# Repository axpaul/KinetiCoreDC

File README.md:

# KinetiCoreDC

🌐 **Langue / Language :** [🇫🇷 Français](README.md) | [🇬🇧 English](README.en.md)

---

**KinetiCoreDC** est un contrôleur de moteur DC durci en boucle fermée permettant de transformer tout moteur à balais en un **servomoteur intelligent** (asservissement en position, vitesse et couple). Développé par **Paul Miailhe** pour **Berry Rocket**.

© 2025/2026 - **Paul Miailhe** (*Berry Rocket*).  
This material is licensed under the **CERN Open Hardware Licence Version 2 - Strongly Reciprocal (CERN-OHL-S)**. $\rightarrow$ [LICENSE](LICENSE)

---

## 1. Vue d'ensemble & Applications

Articulée autour d'un microcontrôleur **STM32G070CBT6** (ARM Cortex-M0+ @ $64\text{ MHz}$, horloge interne HSI) et d'un pont en H intégré **DRV8874PWPR**, la carte intègre l'ensemble de l'électronique de puissance, de protection et de conditionnement nécessaire au pilotage précis d'un actionneur DC en environnement embarqué :

- **Servomoteur numérique multi-axes :** Asservissement PID (position / vitesse / couple) piloté et supervisé sur bus différentiel RS-485 (`THVD1400D`, jusqu'à $500\text{ kbps}$).
- **Actionnement sécurisé ou redondant :** Pilotage par consigne PWM ou impulsion RC ($1\text{–}2\text{ ms}$) via deux entrées opto-isolées (`TLP2310`) autorisant une voie de commande secondaire de secours.
- **Mécatronique & Robotique mobile :** Contrôle de moteurs DC avec retour d'encodeur absolu (`AS5047P`, `AS5600`) ou incrémental Hall, prise d'origine (*homing*) sur butées mécaniques et limitation d'effort par mesure de courant (`IPROPI`).

---

## 2. Caractéristiques électriques

L'étage d'entrée est dimensionné pour une alimentation sur batterie **LiPo 2S ou 3S** (ou source DC régulée). Un contrôleur **LTC4365TS8** associé à deux MOSFETs N-Channel tête-bêche (**SiS412DN**) assure la coupure matérielle en cas de sous-tension, surtension ou inversion de polarité, tandis qu'une diode TVS **SMBJ15CA** protège le régulateur $+3{,}3\text{ V}$ contre les transitoires.

| Paramètre | Symbole | Min | Typ | Max | Unité | Conditions / Notes |
| :--- | :--- | :---: | :---: | :---: | :---: | :--- |
| **Tension d'entrée** | $V_{\text{IN}}$ | $5{,}90$ | $7{,}4\text{–}11{,}1$ | **$14{,}75$** | $\text{V}$ | Compatible LiPo 2S ($8{,}4\text{ V}$) et 3S ($12{,}6\text{ V}$) |
| **Tenue inversion polarité** | $V_{\text{REV}}$ | **$-40$** | — | — | $\text{V}$ | Blocage par N-MOSFETs tête-bêche |
| **Seuil sous-tension (coupure)** | $V_{\text{UVLO}}$ | — | $5{,}90$ | — | $\text{V}$ | Enclenchement à $6{,}20\text{ V}$ (config. défaut) |
| **Seuil surtension (coupure)** | $V_{\text{OVLO}}$ | — | **$14{,}75$** | — | $\text{V}$ | Réarmement à $14{,}01\text{ V}$ (TVS `SMBJ15CA`) |
| **Courant moteur régulé** | $I_{\text{TRIP}}$ | — | **$2{,}6$** | **$2{,}6$** | $\text{A}$ | $V_{\text{REF}} = 2{,}50\text{ V}$, $R_{\text{IPROPI}} = 2{,}49\text{ k}\Omega$ |
| **Courant moteur crête** | $I_{\text{PEAK}}$ | — | — | **$6{,}0$** | $\text{A}$ | Limite silicium `DRV8874` (`XT30` : $15\text{ A}$ cont.) |
| **Puissance d'entrée** | $P_{\text{IN}}$ | — | $32{,}8$ | $38{,}4$ | $\text{W}$ | À $I_{\text{TRIP}} = 2{,}6\text{ A}$ (jusqu'à $88{,}5\text{ W}$ crête à $6\text{ A}$) |
| **Rail logique** | $V_{\text{3V3}}$ | $3{,}28$ | $3{,}30$ | $3{,}32$ | $\text{V}$ | Précision $\pm 0{,}4\text{ \%}$ (`MCP1703A`, boîtier SOT-223) |
| **Courant disponible $+3{,}3\text{ V}$** | $I_{\text{OUT(3V3)}}$ | — | — | **$250$** | $\text{mA}$ | Total carte ($\approx 50\text{ mA}$) + capteurs externes |
| **Courant de veille** | $I_{\text{SHDN}}$ | — | — | **$< 10$** | $\mu\text{A}$ | Broche `SHDN_EXT` tirée à `GND` |

> **Ajustement des seuils :** La fenêtre de protection UVLO/OVLO peut être adaptée à un profil batterie spécifique (LiPo 2S dédié $6{,}45\text{–}10{,}84\text{ V}$, LiPo 3S dédié $9{,}15\text{–}14{,}28\text{ V}$ ou pile 9V) via le pont diviseur du `LTC4365` sur la feuille `Power.kicad_sch`. Le seuil de courant $I_{\text{TRIP}}$ est également ajustable jusqu'à $6\text{ A}$ via `R_IPROPI`.

---

## 3. Interfaces & Capteurs supportés

Toutes les entrées/sorties externes sont équipées de protections contre les décharges électrostatiques (ESD), les inversions de câblage et le bruit de découpage moteur ($32\text{ kHz}$). Les départs d'alimentation $+3{,}3\text{ V}$ vers les capteurs externes (`J10` et `J12`) sont protégés par des résistances série de $22\ \Omega$, tandis que les signaux mécaniques sont filtrés matériellement puis remis en forme par des triggers de Schmitt (**SN74LVC2G14DBV**).

| Connecteur | Interface | Signal / Protocole | Conditionnement & Protection | Compatibilité |
| :--- | :--- | :--- | :--- | :--- |
| **`J2` / `J3`** | `XT30PW-M` (2 pts) | Puissance $V_{\text{IN}}$ / Moteur | TVS `SMBJ15CA`, N-MOSFETs, LEDs sens/PWM | LiPo 2S–3S, moteur DC à balais |
| **`J11`** | `JST-GH` (3 pts) | RS-485 Half-Duplex ($\le 500\text{ kbps}$) | `THVD1400D`, terminaison $120\ \Omega$, TVS `SM712` | Bus multi-axes, télémétrie |
| **`J7` / `J8`** | `JST-GH` (2 pts) | $2\times$ PWM / GPIO isolés ($3{,}3\text{–}5\text{ V}$) | Optocoupleurs `TLP2310`, clamp inverse `SMF6.0A` | Consigne PWM/RC, voie redondante |
| **`J12`** | `JST-GH` (6 pts) | Bus hybride `SPI2` ou `I2C1` | TVS `ESD224DQA` ($0{,}5\text{ pF}$), $+3{,}3\text{ V}$ ($22\ \Omega$), pull-ups `DNP` | **AS5047P**, **AS5048A**, **MA730**, **AS5600** |
| **`J10`** | `JST-GH` (4 pts) | Encodeur quadrature A/B ($3{,}3\text{–}5\text{ V}$) | `USBLC6-2SC6`, $+3{,}3\text{ V}$ ($22\ \Omega$), RC ($160\text{ kHz}$) + Schmitt | Encodeurs incrémentaux à effet Hall |
| **`J4` / `J5`** | `JST-GH` (2 pts) | $2\times$ Fins de course (contact sec) | Pull-up $2{,}2\text{ k}\Omega$, RC ($160\text{ Hz}$) + Schmitt | Butées mécaniques Min / Max |
| **`J9`** | `JST-GH` (3 pts) | Activation carte (`SHDN_EXT`) | Commande directe broche `SHDN` du `LTC4365` | Interrupteur marche / veille |
| **`J6`** | `JST-GH` (2 pts) | Sortie défaut alim (`NFAULT_EXT`) | Drain ouvert actif bas (`LTC4365`) | Supervision système hôte |
| **`J1`** | `TC2070-NL` (14 pts) | SWD + NRST + UART VCP (`USART3`) | Empreinte sans composants (STDC14) | ST-LINK/V3 (flash & debug) |

Pour les capteurs de position absolue sur **`J12`**, le bus fonctionne par défaut en **SPI haute vitesse** (recommandé en environnement bruité pour les **AS5047P** / **MA730**). Il peut être basculé en **I²C** pour un **AS5600** en soudant les deux résistances de pull-up de $4{,}7\text{ k}\Omega$ prévues sur la feuille `Connector.kicad_sch`.

---

## 4. Brochage MCU (`STM32G070CBT6` — LQFP48)

L'affectation des broches du microcontrôleur a été optimisée pour aligner les signaux du pont en H sur le flanc droit du boîtier LQFP48, isoler les canaux analogiques (`ADC_VM` et `IPROPI`) et supprimer tout croisement de pistes vers les connecteurs périphériques.

| Bloc fonctionnel | Signal | Broche | Périphérique | Fonction |
| :--- | :--- | :---: | :--- | :--- |
| **Driver Moteur** | `PH/IN2_MCU` | `PA8` (28) | `TIM1_CH1` | Direction (`PH`) ou PWM secondaire |
| | `EN/IN1_MCU` | `PA9` (29) | `TIM1_CH2` | PWM principale moteur ($32\text{ kHz}$) |
| | `NSLEEP_MCU` | `PC6` (30) | `GPIO_Output` | Activation / Veille du pont en H |
| | `PMODE_MCU` | `PC7` (31) | `GPIO_Output` | Mode `PH/EN` (`0`) ou `PWM` (`1`) |
| | `NFAULT_MCU` | `PA10` (32) | `GPIO_EXTI10` | Interruption défaut driver (front descendant) |
| | `IPROPI_MCU` | `PB10` (22) | `ADC1_IN11` | Lecture courant moteur ($1{,}13\text{ V/A}$, filtre RC) |
| **Supervision** | `ADC_VM` | `PB2` (21) | `ADC1_IN10` | Mesure tension d'entrée $V_M$ |
| **RS-485** | `RS485_DE` / `TX` / `RX` | `PA1`, `PA2`, `PA3` | `USART2` (+ DMA) | Bus différentiel avec contrôle DE matériel |
| **Encodeur** | `TIM_ENC_A` / `B` | `PA6` (17), `PA7` (18) | `TIM3_CH1/CH2` | Décodage quadrature matériel X4 |
| **Optocoupleurs** | `OPTO1_MCU` / `OPTO2_MCU` | `PB14` (26), `PB15` (27) | `TIM15_CH1/CH2` | Input Capture PWM / Consigne redondante |
| **Fins de course** | `TRIG1_MCU` / `TRIG2_MCU` | `PD2` (40), `PD3` (41) | `GPIO_EXTI2/EXTI3` | Interruptions butées (front montant) |
| **Bus Capteur** | `MISO`/`MOSI`/`SCK`/`NSS` | `PB6`..`PB9` (45–48) | `SPI2` (ou `I2C1`) | Encodeur magnétique absolu |
| **IHM** | `BLUE` / `RED` / `GREEN` | `PC13`, `PC14`, `PC15` | `GPIO_Output` | LED RGB 8 couleurs (anode commune, actif bas) |
| | `BUZZER_MCU` | `PA4` (15) | `TIM14_CH1` | Signal piézo PWM $4\text{ kHz}$ |
| **Debug** | `SWDIO` / `SWCLK` | `PA13` (35), `PA14` (36) | `SYS_SWD` | Programmation et débogage |
| | `VPC_TX` / `VPC_RX` | `PA5` (16), `PB0` (19) | `USART3_TX/RX` | Console série virtuelle de diagnostic |

---

## 5. Architecture KiCad & Structure du dépôt

Le projet est conçu sous **KiCad 10.0** autour d'une feuille racine et de trois sous-feuilles hiérarchiques, accompagnées du fichier de configuration **STM32CubeMX** (`KinetiCoreDC.ioc`) :

```text
KinetiCoreDC/
├── KinetiCoreDC.kicad_pro       # Projet KiCad 10.0
├── KinetiCoreDC.kicad_sch       # Feuille 1/4 : MCU STM32G070CBT6 & hiérarchie
├── Interface.kicad_sch          # Feuille 2/4 : RS-485, optocoupleurs, encodeur, butées
├── Power.kicad_sch              # Feuille 3/4 : LTC4365, LDO 3.3V, DRV8874, RGB, buzzer
├── Connector.kicad_sch          # Feuille 4/4 : XT30, JST-GH, Tag-Connect, ESD224DQA
├── KinetiCoreDC.kicad_pcb       # Routage PCB
├── KinetiCoreDC.ioc             # Configuration matérielle STM32CubeMX
├── Datasheet/                   # Fiches techniques des composants
├── lib/                         # Symboles, empreintes et modèles 3D locaux
├── README.md                    # Documentation française
├── README.en.md                 # Documentation anglaise
└── LICENSE                      # Licence CERN-OHL-S-2.0

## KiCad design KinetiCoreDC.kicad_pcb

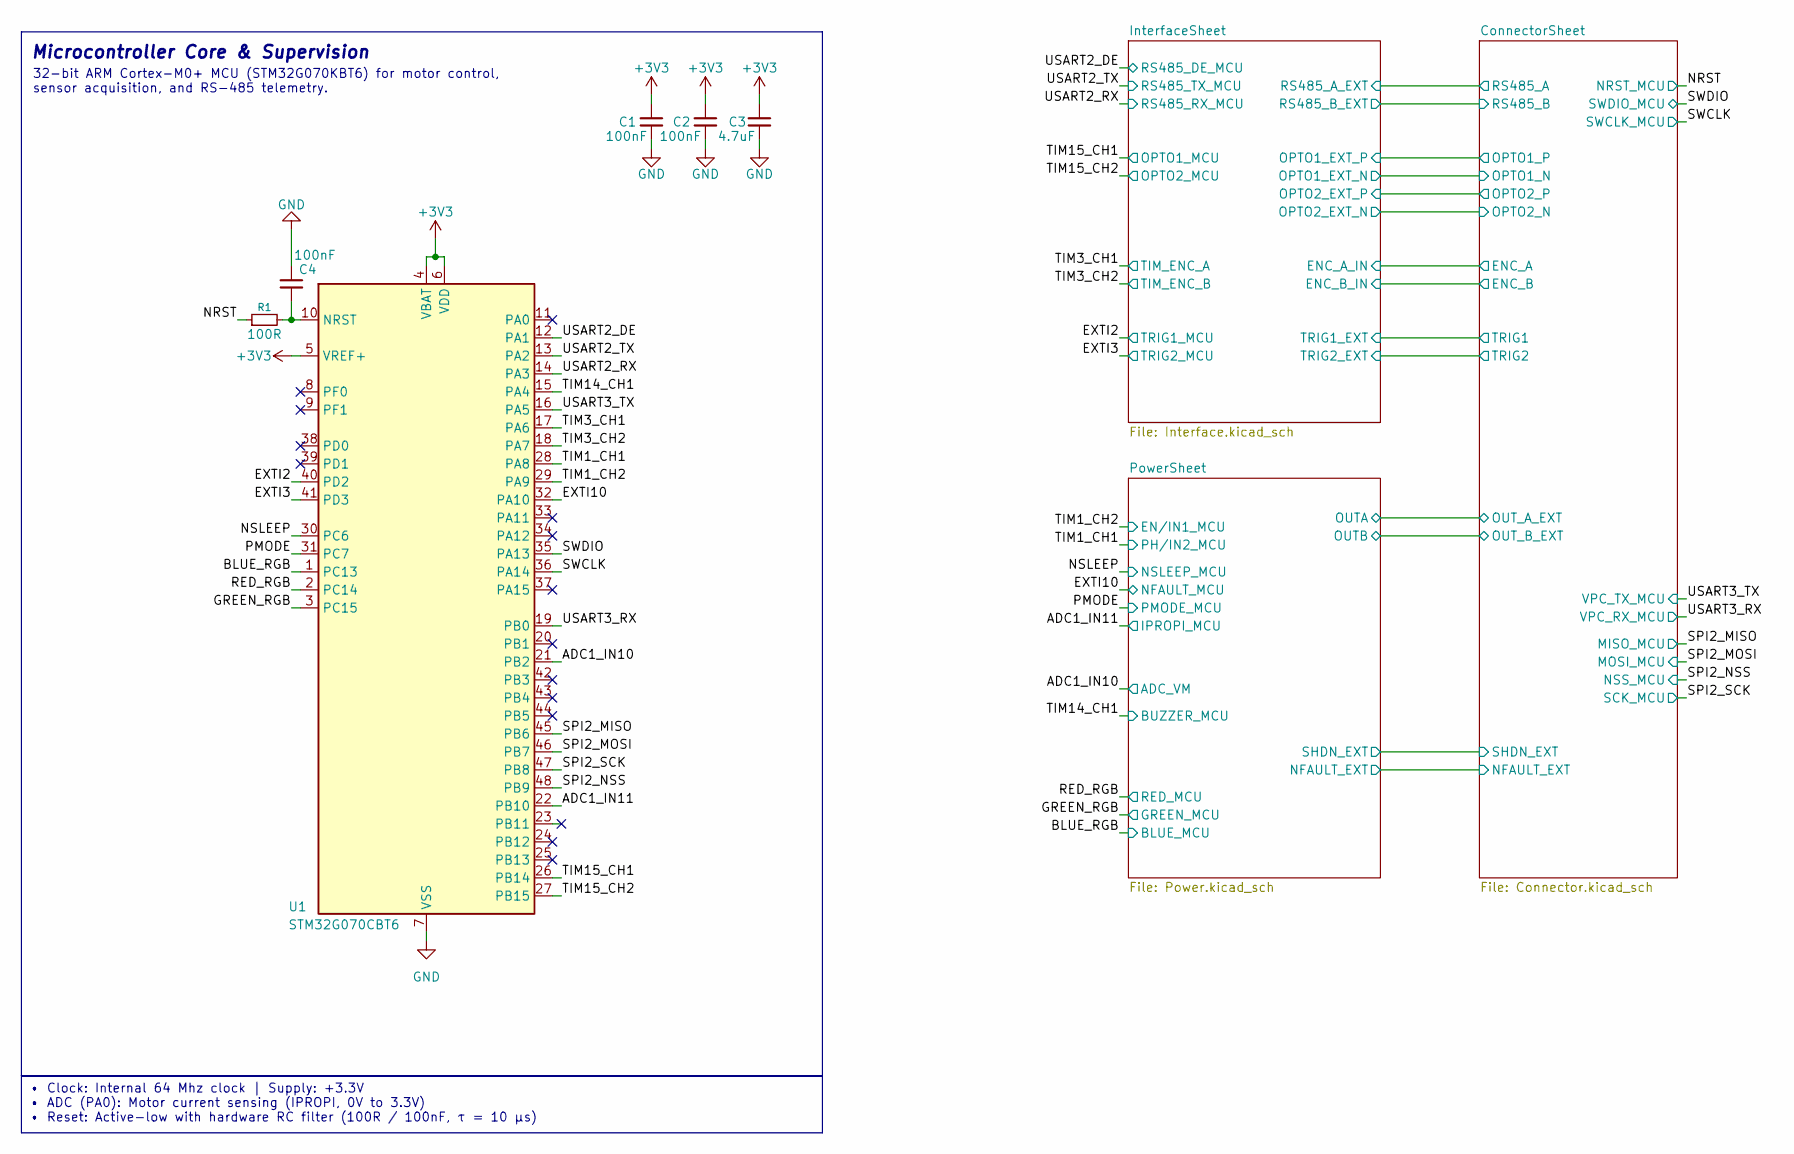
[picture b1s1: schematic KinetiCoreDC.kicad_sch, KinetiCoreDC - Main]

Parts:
C1, C2, C4: 100nF; C_0603_1608Metric
C3: 4.7uF; C_0603_1608Metric
R1: 100R; R_0603_1608Metric
U1: STM32G070CBT6; LQFP-48_7x7mm_P0.5mm

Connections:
+3V3: C1.1, C2.1, C3.1, U1.4 (VBAT), U1.5 (VREF+), U1.6 (VDD); also elsewhere on the board
/ADC1_IN10: U1.21 (PB2); also elsewhere on the board
/ADC1_IN11: U1.22 (PB10); also elsewhere on the board
/BLUE_RGB: U1.1 (PC13); also elsewhere on the board
/EXTI2: U1.40 (PD2); also elsewhere on the board
/EXTI3: U1.41 (PD3); also elsewhere on the board
/EXTI10: U1.32 (PA10); also elsewhere on the board
/GREEN_RGB: U1.3 (PC15); also elsewhere on the board
/NRST: R1.1; also elsewhere on the board
/NSLEEP: U1.30 (PC6); also elsewhere on the board
/PMODE: U1.31 (PC7); also elsewhere on the board
/RED_RGB: U1.2 (PC14); also elsewhere on the board
/SPI2_MISO: U1.45 (PB6); also elsewhere on the board
/SPI2_MOSI: U1.46 (PB7); also elsewhere on the board
/SPI2_NSS: U1.48 (PB9); also elsewhere on the board
/SPI2_SCK: U1.47 (PB8); also elsewhere on the board
/SWCLK: U1.36 (PA14); also elsewhere on the board
/SWDIO: U1.35 (PA13); also elsewhere on the board
/TIM1_CH1: U1.28 (PA8); also elsewhere on the board
/TIM1_CH2: U1.29 (PA9); also elsewhere on the board
/TIM3_CH1: U1.17 (PA6); also elsewhere on the board
/TIM3_CH2: U1.18 (PA7); also elsewhere on the board
/TIM14_CH1: U1.15 (PA4); also elsewhere on the board
/TIM15_CH1: U1.26 (PB14); also elsewhere on the board
/TIM15_CH2: U1.27 (PB15); also elsewhere on the board
/USART2_DE: U1.12 (PA1); also elsewhere on the board
/USART2_RX: U1.14 (PA3); also elsewhere on the board
/USART2_TX: U1.13 (PA2); also elsewhere on the board
/USART3_RX: U1.19 (PB0); also elsewhere on the board
/USART3_TX: U1.16 (PA5); also elsewhere on the board
GND: C1.2, C2.2, C3.2, C4.2, U1.7 (VSS); also elsewhere on the board
unnamed: C4.1, R1.2, U1.10 (NRST)

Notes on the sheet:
Microcontroller Core & Supervision
32-bit ARM Cortex-M0+ MCU (STM32G070KBT6) for motor control, sensor acquisition, and RS-485 telemetry.
• Clock: Internal 64 Mhz clock | Supply: +3.3V • ADC (PA0): Motor current sensing (IPROPI, 0V to 3.3V) • Reset: Active-low with hardware RC filter (100R / 100nF, τ = 10 µs)

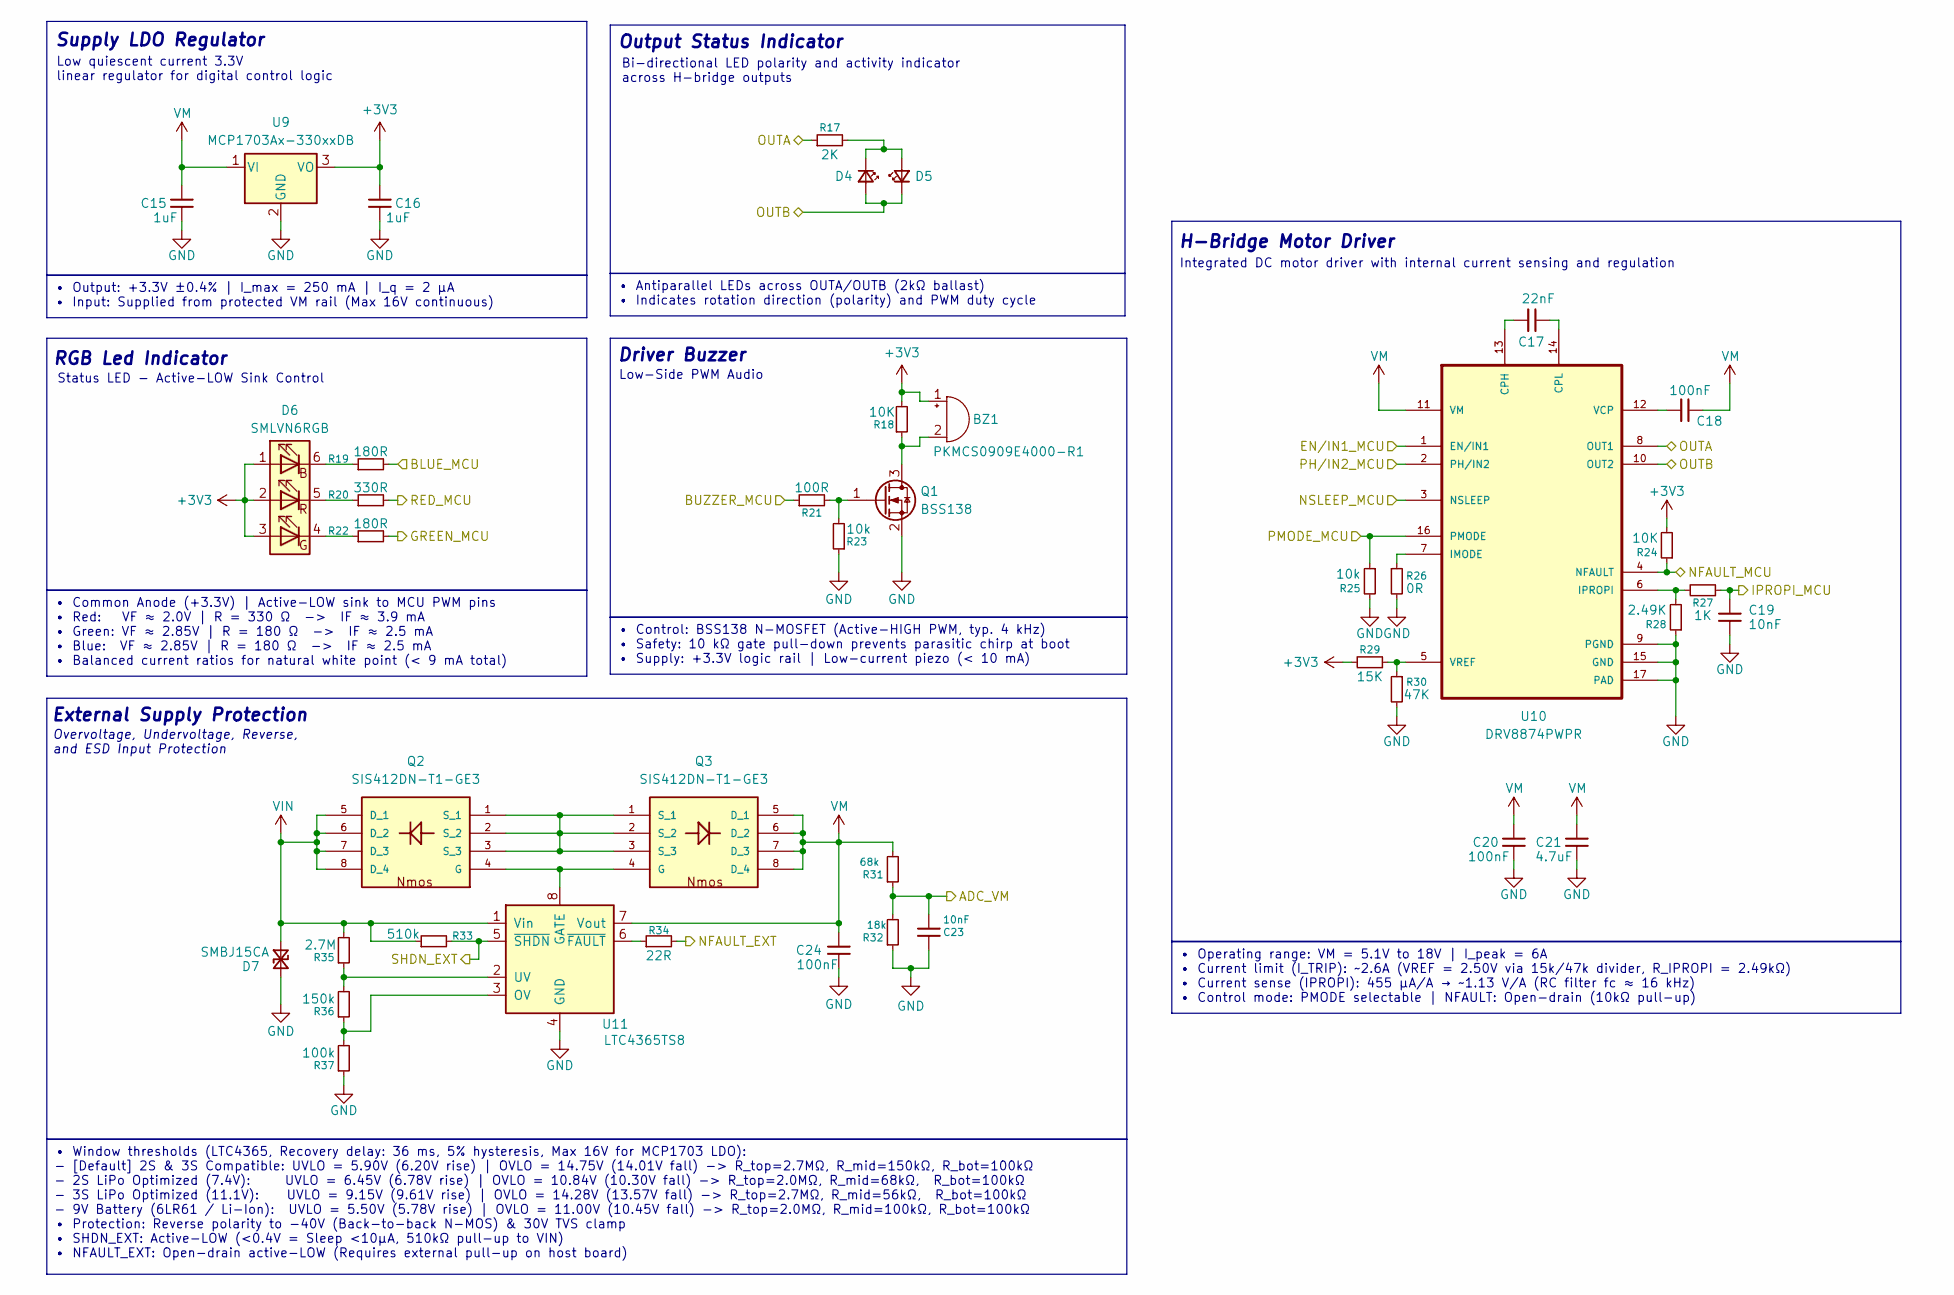
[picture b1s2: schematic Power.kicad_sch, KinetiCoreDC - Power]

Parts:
BZ1: PKMCS0909E4000-R1; Buzzer_Murata_PKMCS0909E
C15, C16: 1uF; C_0805_2012Metric
C17: 22nF; C_0603_1608Metric
C18, C24: 100nF; C_0603_1608Metric
C19, C23: 10nF; C_0603_1608Metric
C20: 100nF; C_0805_2012Metric
C21: 4.7uF; C_0805_2012Metric
D4, D5: LED_Small; LED_0603_1608Metric
D6: SMLVN6RGB; LED_ROHM_SMLVN6
D7: SMBJ15CA; D_SMA
Q1: BSS138; SOT-23
Q2, Q3: SIS412DN-T1-GE3; POWERPAK-1212-8; MOUSER_PART_NUMBER 781-SIS412DN-T1-GE3
R17: 2K; R_0603_1608Metric
R18, R24: 10K; R_0603_1608Metric
R19, R22: 180R; R_0603_1608Metric
R20: 330R; R_0603_1608Metric
R21: 100R; R_0603_1608Metric
R23, R25: 10k; R_0603_1608Metric
R26: 0R; R_0603_1608Metric
R27: 1K; R_0603_1608Metric
R28: 2.49K; R_0603_1608Metric
R29: 15K; R_0603_1608Metric
R30: 47K; R_0603_1608Metric
R31: 68k; R_0603_1608Metric
R32: 18k; R_0603_1608Metric
R33: 510k; R_0603_1608Metric
R34: 22R; R_0603_1608Metric
R35: 2.7M; R_0603_1608Metric
R36: 150k; R_0603_1608Metric
R37: 100k; R_0603_1608Metric
U9: MCP1703Ax-330xxDB; SOT-223-3_TabPin2
U10: DRV8874PWPR; SOP65P640X120-17N
U11: LTC4365TS8; TSOT-23-8

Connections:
+3V3: BZ1.1 (+), C16.1, D6.1 (BA), D6.2 (RA), D6.3 (GA), R18.2, R24.2, R29.2, U9.3 (VO); also elsewhere on the board
/ADC1_IN10: C23.2, R31.1, R32.2; also elsewhere on the board
/ADC1_IN11: C19.2, R27.1; also elsewhere on the board
/BLUE_RGB: R19.2; also elsewhere on the board
/ConnectorSheet/NFAULT_EXT: R34.2; also elsewhere on the board
/ConnectorSheet/OUT_A_EXT: R17.1, U10.8 (OUT1); also elsewhere on the board
/ConnectorSheet/OUT_B_EXT: D4.2 (A), D5.1 (K), U10.10 (OUT2); also elsewhere on the board
/ConnectorSheet/SHDN_EXT: R33.2, U11.5 (~SHDN); also elsewhere on the board
/EXTI10: R24.1, U10.4 (NFAULT); also elsewhere on the board
/GREEN_RGB: R22.2; also elsewhere on the board
/NSLEEP: U10.3 (NSLEEP); also elsewhere on the board
/PMODE: R25.1, U10.16 (PMODE); also elsewhere on the board
/RED_RGB: R20.2; also elsewhere on the board
/TIM1_CH1: U10.2 (PH/IN2); also elsewhere on the board
/TIM1_CH2: U10.1 (EN/IN1); also elsewhere on the board
/TIM14_CH1: R21.1; also elsewhere on the board
GND: C15.2, C16.2, C19.1, C20.2, C21.2, C23.1, C24.2, D7.2 (A2), Q1.2 (S), R23.1, R25.2, R26.2, R28.1, R30.2, R32.1, R37.1, U9.2 (GND), U10.9 (PGND), U10.15 (GND), U10.17 (PAD), U11.4 (GND); also elsewhere on the board
unnamed: BZ1.2 (-), Q1.3 (D), R18.1
unnamed: D4.1 (K), D5.2 (A), R17.2
unnamed: D6.6 (BK), R19.1
unnamed: D6.4 (GK), R22.1
unnamed: D6.5 (RK), R20.1
unnamed: Q1.1 (G), R21.2, R23.2
unnamed: Q2.4 (G), Q3.4 (G), U11.8 (GATE)
unnamed: Q2.1 (S_1), Q2.2 (S_2), Q2.3 (S_3), Q3.1 (S_1), Q3.2 (S_2), Q3.3 (S_3)
unnamed: C17.1, U10.13 (CPH)
unnamed: C17.2, U10.14 (CPL)
unnamed: R26.1, U10.7 (IMODE)
unnamed: R27.2, R28.2, U10.6 (IPROPI)
unnamed: C18.1, U10.12 (VCP)
unnamed: R29.1, R30.1, U10.5 (VREF)
unnamed: R36.1, R37.2, U11.3 (OV)
unnamed: R35.1, R36.2, U11.2 (UV)
unnamed: R34.1, U11.6 (~FAULT)
VIN: D7.1 (A1), Q2.5 (D_1), Q2.6 (D_2), Q2.7 (D_3), Q2.8 (D_4), R33.1, R35.2, U11.1 (Vin); also elsewhere on the board
VM: C15.1, C18.2, C20.1, C21.1, C24.1, Q3.5 (D_1), Q3.6 (D_2), Q3.7 (D_3), Q3.8 (D_4), R31.2, U9.1 (VI), U10.11 (VM), U11.7 (Vout)

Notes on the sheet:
H-Bridge Motor Driver
RGB Led Indicator
Low quiescent current 3.3V linear regulator for digital control logic
Low-Side PWM Audio
Output Status Indicator
Driver Buzzer
Supply LDO Regulator
Overvoltage, Undervoltage, Reverse, and ESD Input Protection
Integrated DC motor driver with internal current sensing and regulation
External Supply Protection
Bi-directional LED polarity and activity indicator across H-bridge outputs
Status LED - Active-LOW Sink Control
• Control: BSS138 N-MOSFET (Active-HIGH PWM, typ. 4 kHz) • Safety: 10 kΩ gate pull-down prevents parasitic chirp at boot • Supply: +3.3V logic rail | Low-current piezo (< 10 mA)
• Window thresholds (LTC4365, Recovery delay: 36 ms, 5% hysteresis, Max 16V for MCP1703 LDO): - [Default] 2S & 3S Compatible: UVLO = 5.90V (6.20V rise) | OVLO = 14.75V (14.01V fall) -> R_top=2.7MΩ, R_mid=150kΩ, R_bot=100kΩ - 2S LiPo Optimized (7.4V): UVLO = 6.45V (6.78V rise) | OVLO = 10.84V (10.30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
• Output: +3.3V ±0.4% | I_max = 250 mA | I_q = 2 µA • Input: Supplied from protected VM rail (Max 16V continuous)
• Antiparallel LEDs across OUTA/OUTB (2kΩ ballast) • Indicates rotation direction (polarity) and PWM duty cycle
• Operating range: VM = 5.1V to 18V | I_peak = 6A • Current limit (I_TRIP): ~2.6A (VREF = 2.50V via 15k/47k divider, R_IPROPI = 2.49kΩ) • Current sense (IPROPI): 455 µA/A → ~1.13 V/A (RC filter fc ≈ 16 kHz) • Control mode: PMODE selectable | NFAULT: Open-drain (10kΩ pull-up)
• Common Anode (+3.3V) | Active-LOW sink to MCU PWM pins • Red: VF ≈ 2.0V | R = 330 Ω -> IF ≈ 3.9 mA • Green: VF ≈ 2.85V | R = 180 Ω -> IF ≈ 2.5 mA • Blue: VF ≈ 2.85V | R = 180 Ω -> IF ≈ 2.5 mA • Balanced current ratios for natural white point (< 9 mA total)

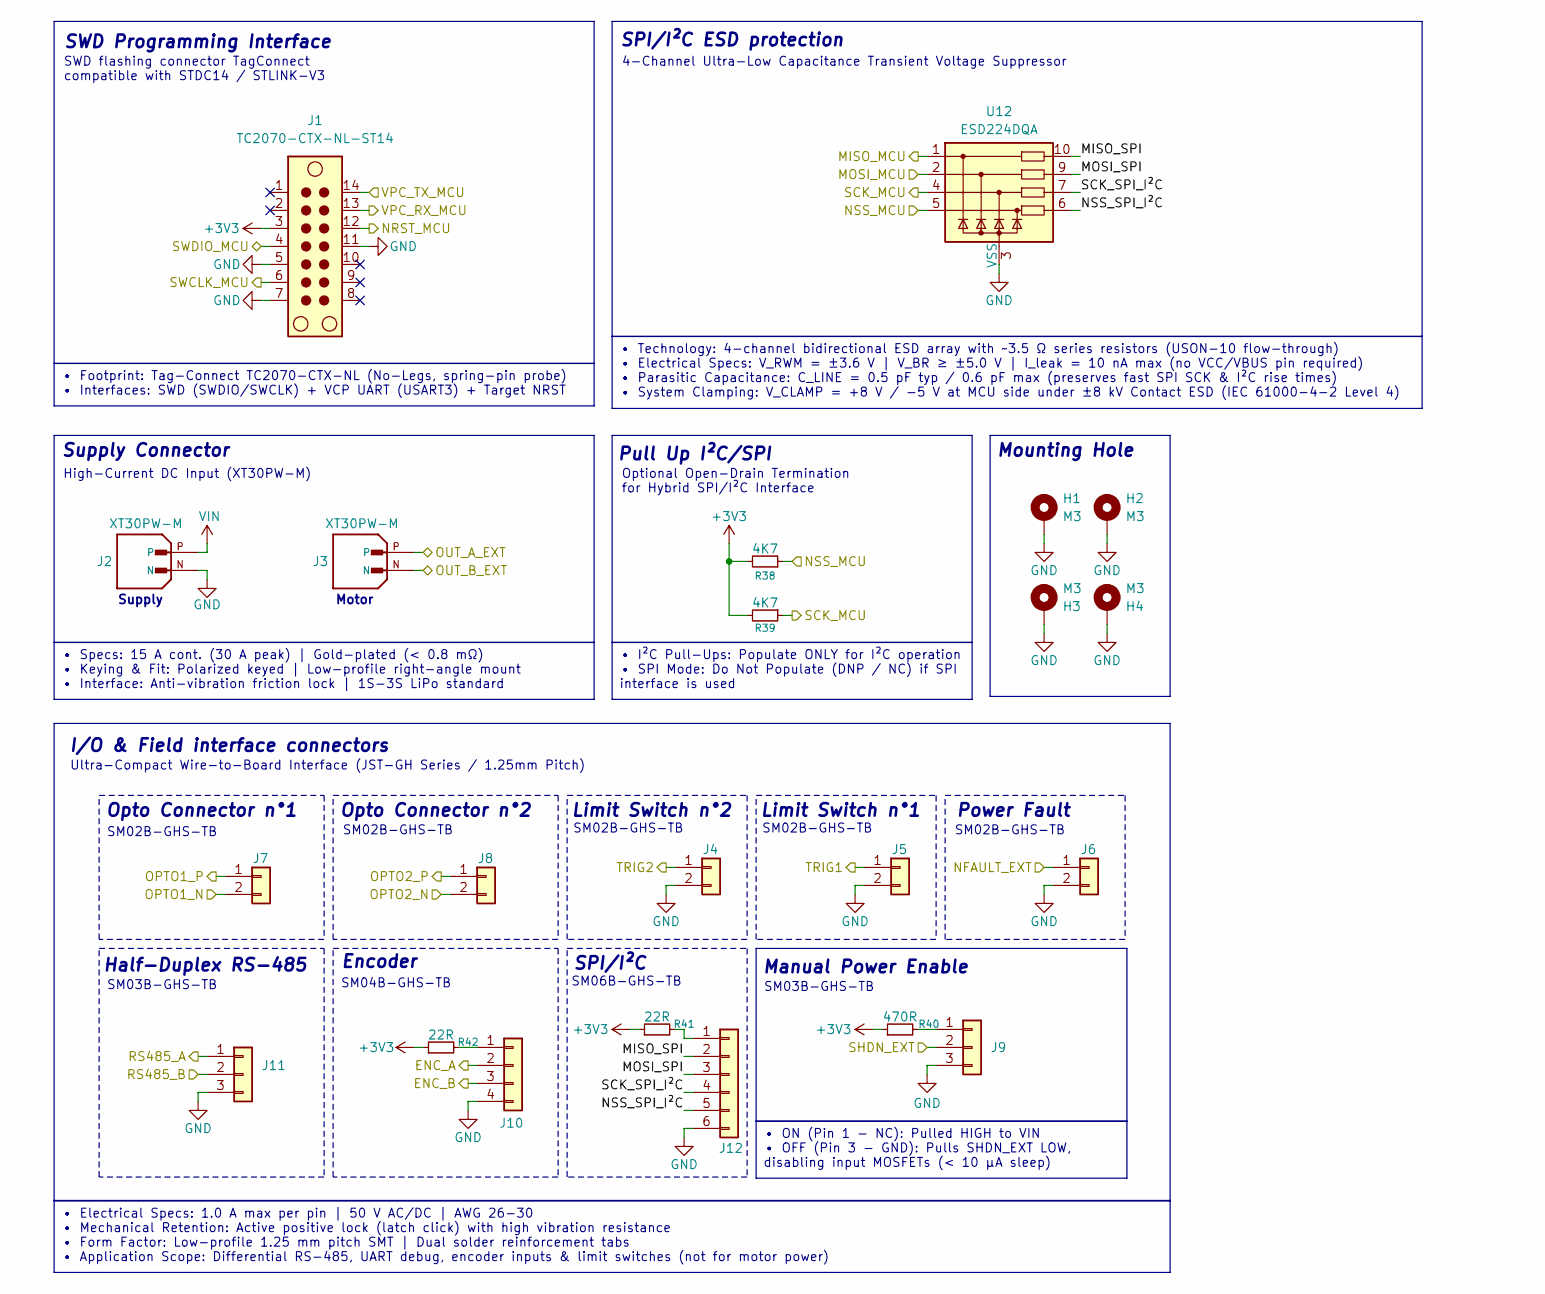
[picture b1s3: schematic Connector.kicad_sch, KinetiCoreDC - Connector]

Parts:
H1, H2, H3, H4: M3; MountingHole_3.2mm_M3_DIN965_Pad_TopBottom
J1: TC2070-CTX-NL-ST14; Tag-Connect_TC2070-IDC-FP_2x07_P1.27mm_Vertical
J2, J3: XT30PW-M; AMASS_XT30PW-M; PARTREV 1.2
J4, J5, J6, J7: SM02B-GHS-TB; JST_GH_SM02B-GHS-TB_1x02-1MP_P1.25mm_Horizontal
J8: BM02B-GHS-TBT; JST_GH_SM02B-GHS-TB_1x02-1MP_P1.25mm_Horizontal
J9, J11: SM03B-GHS-TB; JST_GH_SM03B-GHS-TB_1x03-1MP_P1.25mm_Horizontal
J10: SM04B-GHS-TB; JST_GH_SM04B-GHS-TB_1x04-1MP_P1.25mm_Horizontal
J12: Conn_01x06; JST_GH_SM06B-GHS-TB_1x06-1MP_P1.25mm_Horizontal
R38, R39: 4K7; R_0603_1608Metric
R40: 470R; R_0603_1608Metric
R41, R42: 22R; R_0603_1608Metric
U12: ESD224DQA; Diodes_UDFN-10_1x2.5mm_P0.5mm

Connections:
+3V3: J1.3, R38.2, R39.2, R40.1, R41.1, R42.1; also elsewhere on the board
/ConnectorSheet/ENC_A: J10.2; also elsewhere on the board
/ConnectorSheet/ENC_B: J10.3; also elsewhere on the board
/ConnectorSheet/MISO_SPI: J12.2, U12.10
/ConnectorSheet/MOSI_SPI: J12.3, U12.9
/ConnectorSheet/NFAULT_EXT: J6.1; also elsewhere on the board
/ConnectorSheet/NSS_SPI_I²C: J12.5, U12.6
/ConnectorSheet/OPTO1_N: J7.2; also elsewhere on the board
/ConnectorSheet/OPTO1_P: J7.1; also elsewhere on the board
/ConnectorSheet/OPTO2_N: J8.2; also elsewhere on the board
/ConnectorSheet/OPTO2_P: J8.1; also elsewhere on the board
/ConnectorSheet/OUT_A_EXT: J3.P; also elsewhere on the board
/ConnectorSheet/OUT_B_EXT: J3.N; also elsewhere on the board
/ConnectorSheet/RS485_A: J11.1; also elsewhere on the board
/ConnectorSheet/RS485_B: J11.2; also elsewhere on the board
/ConnectorSheet/SCK_SPI_I²C: J12.4, U12.7
/ConnectorSheet/SHDN_EXT: J9.2; also elsewhere on the board
/ConnectorSheet/TRIG1: J5.1; also elsewhere on the board
/ConnectorSheet/TRIG2: J4.1; also elsewhere on the board
/NRST: J1.12; also elsewhere on the board
/SPI2_MISO: U12.1; also elsewhere on the board
/SPI2_MOSI: U12.2; also elsewhere on the board
/SPI2_NSS: R38.1, U12.5; also elsewhere on the board
/SPI2_SCK: R39.1, U12.4; also elsewhere on the board
/SWCLK: J1.6; also elsewhere on the board
/SWDIO: J1.4; also elsewhere on the board
/USART3_RX: J1.13; also elsewhere on the board
/USART3_TX: J1.14; also elsewhere on the board
GND: H1.1 (1_1), H2.1 (1_1), H3.1 (1_1), H4.1 (1_1), J1.5, J1.7, J1.11, J2.N, J4.2, J5.2, J6.2, J9.3, J10.4, J11.3, J12.6, U12.3 (VSS), U12.8 (VSS); also elsewhere on the board
unnamed: J9.1, R40.2
unnamed: J10.1, R42.2
unnamed: J12.1, R41.2
VIN: J2.P; also elsewhere on the board

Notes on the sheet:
Limit Switch n°1
Pull Up I²C/SPI
SM03B-GHS-TB
Encoder
Power Fault
I/O & Field interface connectors
Optional Open-Drain Termination for Hybrid SPI/I²C Interface
SPI/I²C
Opto Connector n°1
SM06B-GHS-TB
High-Current DC Input (XT30PW-M)
SM02B-GHS-TB
SWD flashing connector TagConnect compatible with STDC14 / STLINK-V3
4-Channel Ultra-Low Capacitance Transient Voltage Suppressor
Limit Switch n°2
Opto Connector n°2
Mounting Hole
SM04B-GHS-TB
Manual Power Enable
Ultra-Compact Wire-to-Board Interface (JST-GH Series / 1.25mm Pitch)
SPI/I²C ESD protection
Half-Duplex RS-485
Supply Connector
SWD Programming Interface
Supply
Motor
• Footprint: Tag-Connect TC2070-CTX-NL (No-Legs, spring-pin probe) • Interfaces: SWD (SWDIO/SWCLK) + VCP UART (USART3) + Target NRST
• Electrical Specs: 1.0 A max per pin | 50 V AC/DC | AWG 26-30 • Mechanical Retention: Active positive lock (latch click) with high vibration resistance • Form Factor: Low-profile 1.25 mm pitch SMT | Dual solder reinforcement tabs • Application Scope: Differential RS-485, UART debug, encoder inputs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
• Specs: 15 A cont. (30 A peak) | Gold-plated (< 0.8 mΩ) • Keying & Fit: Polarized keyed | Low-profile right-angle mount • Interface: Anti-vibration friction lock | 1S-3S LiPo standard
• Technology: 4-channel bidirectional ESD array with ~3.5 Ω series resistors (USON-10 flow-through) • Electrical Specs: V_RWM = ±3.6 V | V_BR ≥ ±5.0 V | I_leak = 10 nA max (no VCC/VBUS pin required) • Parasitic Capacitance: C_LINE = 0.5 pF typ / 0.6 pF max (preserves fast SPI SCK & I²C rise times) 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
• I²C Pull-Ups: Populate ONLY for I²C operation • SPI Mode: Do Not Populate (DNP / NC) if SPI interface is used
• ON (Pin 1 - NC): Pulled HIGH to VIN • OFF (Pin 3 - GND): Pulls SHDN_EXT LOW, disabling input MOSFETs (< 10 µA sleep)

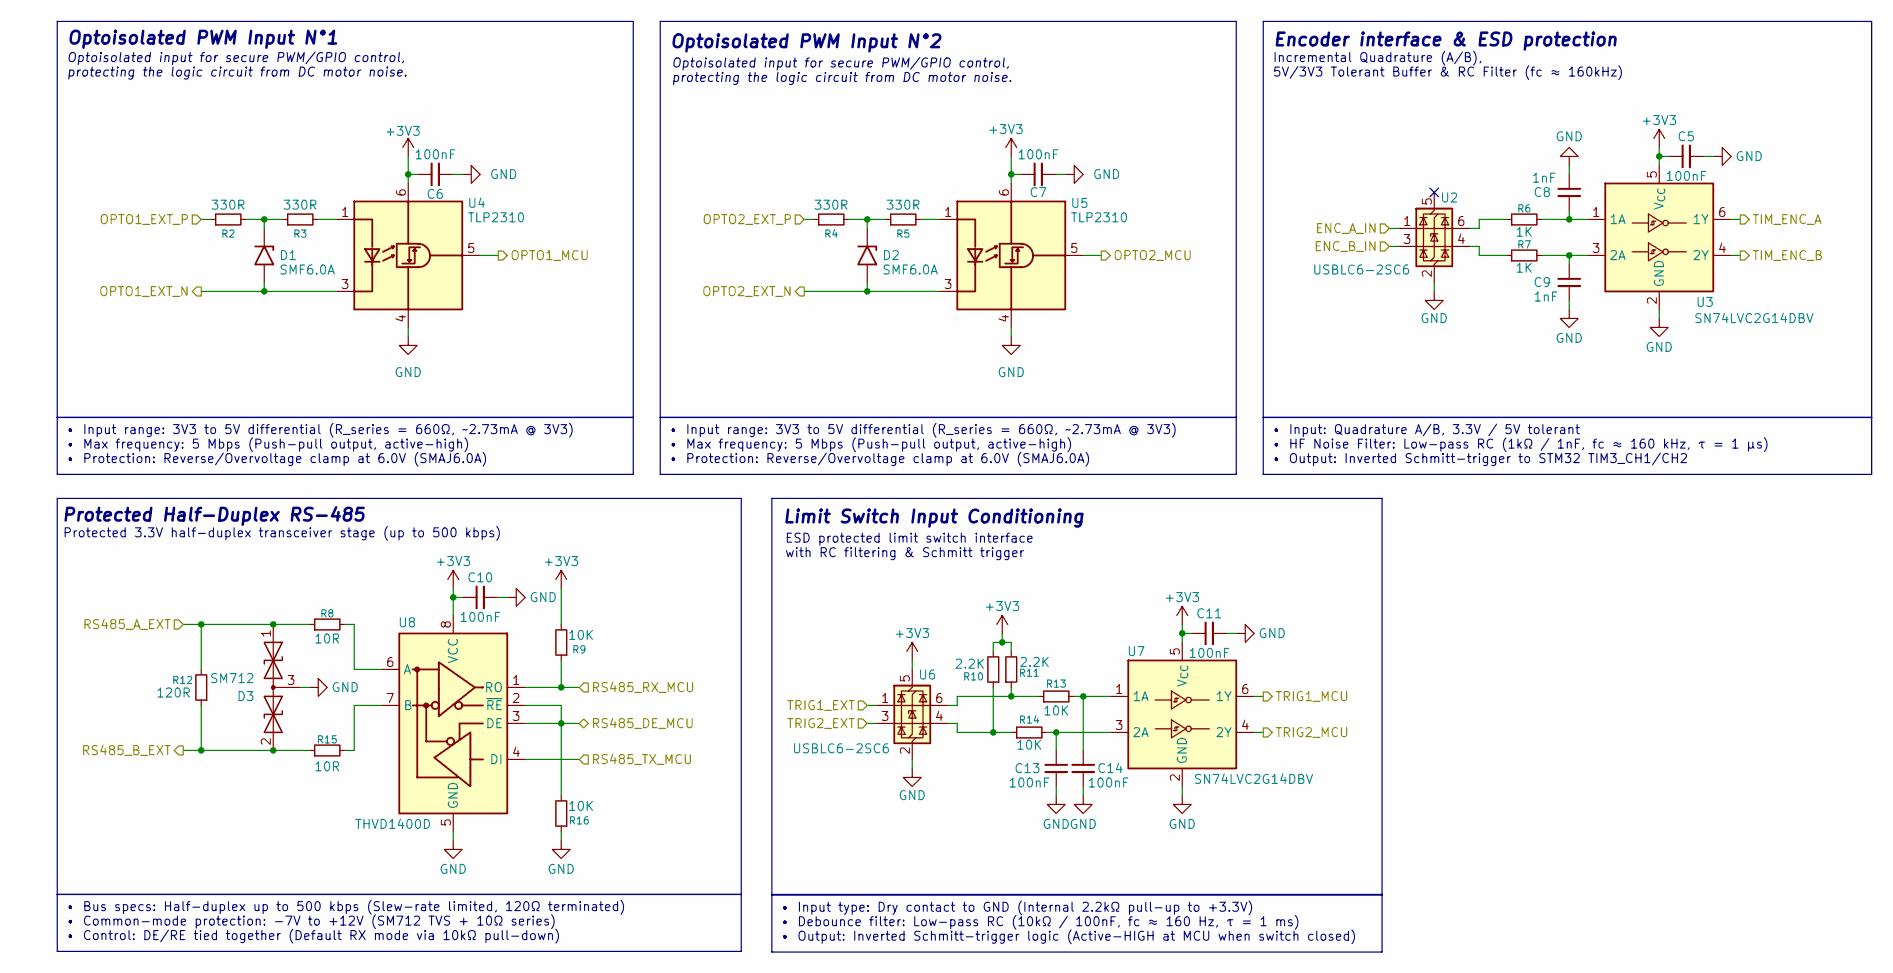
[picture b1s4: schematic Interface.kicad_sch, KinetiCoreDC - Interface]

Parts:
C5, C6, C7, C10, C11, C13, C14: 100nF; C_0603_1608Metric
C8, C9: 1nF; C_0603_1608Metric
D1, D2: SMF6.0A; D_SOD-123F
D3: SM712; SOT-23
R2, R3, R4, R5: 330R; R_0603_1608Metric
R6, R7: 1K; R_0603_1608Metric
R8, R15: 10R; R_0603_1608Metric
R9, R13, R14, R16: 10K; R_0603_1608Metric
R10, R11: 2.2K; R_0603_1608Metric
R12: 120R; R_0603_1608Metric
U2, U6: USBLC6-2SC6; SOT-23-6
U3, U7: SN74LVC2G14DBV; SOT-23-6
U4, U5: TLP2310; SO-5-6_4.55x3.7mm_P1.27mm
U8: THVD1400D; SOIC-8_3.9x4.9mm_P1.27mm

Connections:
+3V3: C5.1, C6.1, C7.1, C10.1, C11.1, R9.2, R10.2, R11.2, U3.5 (V_{CC}), U4.6 (VDD), U5.6 (VDD), U6.5 (VBUS), U7.5 (V_{CC}), U8.8 (VCC); also elsewhere on the board
/ConnectorSheet/ENC_A: U2.1 (I/O1); also elsewhere on the board
/ConnectorSheet/ENC_B: U2.3 (I/O2); also elsewhere on the board
/ConnectorSheet/OPTO1_N: D1.2 (A2), U4.3 (K); also elsewhere on the board
/ConnectorSheet/OPTO1_P: R2.1; also elsewhere on the board
/ConnectorSheet/OPTO2_N: D2.2 (A2), U5.3 (K); also elsewhere on the board
/ConnectorSheet/OPTO2_P: R4.1; also elsewhere on the board
/ConnectorSheet/RS485_A: D3.1 (A1), R8.1, R12.2; also elsewhere on the board
/ConnectorSheet/RS485_B: D3.2 (A2), R12.1, R15.1; also elsewhere on the board
/ConnectorSheet/TRIG1: U6.1 (I/O1); also elsewhere on the board
/ConnectorSheet/TRIG2: U6.3 (I/O2); also elsewhere on the board
/EXTI2: U7.6 (1Y); also elsewhere on the board
/EXTI3: U7.4 (2Y); also elsewhere on the board
/TIM3_CH1: U3.6 (1Y); also elsewhere on the board
/TIM3_CH2: U3.4 (2Y); also elsewhere on the board
/TIM15_CH1: U4.5 (VO); also elsewhere on the board
/TIM15_CH2: U5.5 (VO); also elsewhere on the board
/USART2_DE: R16.2, U8.2 (~RE), U8.3 (DE); also elsewhere on the board
/USART2_RX: R9.1, U8.1 (RO); also elsewhere on the board
/USART2_TX: U8.4 (DI); also elsewhere on the board
GND: C5.2, C6.2, C7.2, C8.1, C9.1, C10.2, C11.2, C13.1, C14.1, D3.3 (common), R16.1, U2.2 (GND), U3.2 (GND), U4.4 (GND), U5.4 (GND), U6.2 (GND), U7.2 (GND), U8.5 (GND); also elsewhere on the board
unnamed: D1.1 (A1), R2.2, R3.1
unnamed: D2.1 (A1), R4.2, R5.1
unnamed: R6.1, U2.6 (I/O1)
unnamed: R7.1, U2.4 (I/O2)
unnamed: R10.1, R14.1, U6.4 (I/O2)
unnamed: R11.1, R13.1, U6.6 (I/O1)
unnamed: C8.2, R6.2, U3.1 (1A)
unnamed: C9.2, R7.2, U3.3 (2A)
unnamed: R3.2, U4.1 (A)
unnamed: R5.2, U5.1 (A)
unnamed: C14.2, R13.2, U7.1 (1A)
unnamed: C13.2, R14.2, U7.3 (2A)
unnamed: R8.2, U8.6 (A)
unnamed: R15.2, U8.7 (B)

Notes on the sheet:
Optoisolated PWM Input N°1
Protected 3.3V half-duplex transceiver stage (up to 500 kbps)
Optoisolated input for secure PWM/GPIO control, protecting the logic circuit from DC motor noise.
Incremental Quadrature (A/B), 5V/3V3 Tolerant Buffer & RC Filter (fc ≈ 160kHz)
Encoder interface & ESD protection
Limit Switch Input Conditioning
ESD protected limit switch interface with RC filtering & Schmitt trigger
Optoisolated PWM Input N°2
Protected Half-Duplex RS-485
• Input: Quadrature A/B, 3.3V / 5V tolerant • HF Noise Filter: Low-pass RC (1kΩ / 1nF, fc ≈ 160 kHz, τ = 1 µs) • Output: Inverted Schmitt-trigger to STM32 TIM3_CH1/CH2
• Bus specs: Half-duplex up to 500 kbps (Slew-rate limited, 120Ω terminated) • Common-mode protection: -7V to +12V (SM712 TVS + 10Ω series) • Control: DE/RE tied together (Default RX mode via 10kΩ pull-down)
• Input type: Dry contact to GND (Internal 2.2kΩ pull-up to +3.3V) • Debounce filter: Low-pass RC (10kΩ / 100nF, fc ≈ 160 Hz, τ = 1 ms) • Output: Inverted Schmitt-trigger logic (Active-HIGH at MCU when switch closed)
• Input range: 3V3 to 5V differential (R_series = 660Ω, ~2.73mA @ 3V3) • Max frequency: 5 Mbps (Push-pull output, active-high) • Protection: Reverse/Overvoltage clamp at 6.0V (SMAJ6.0A)

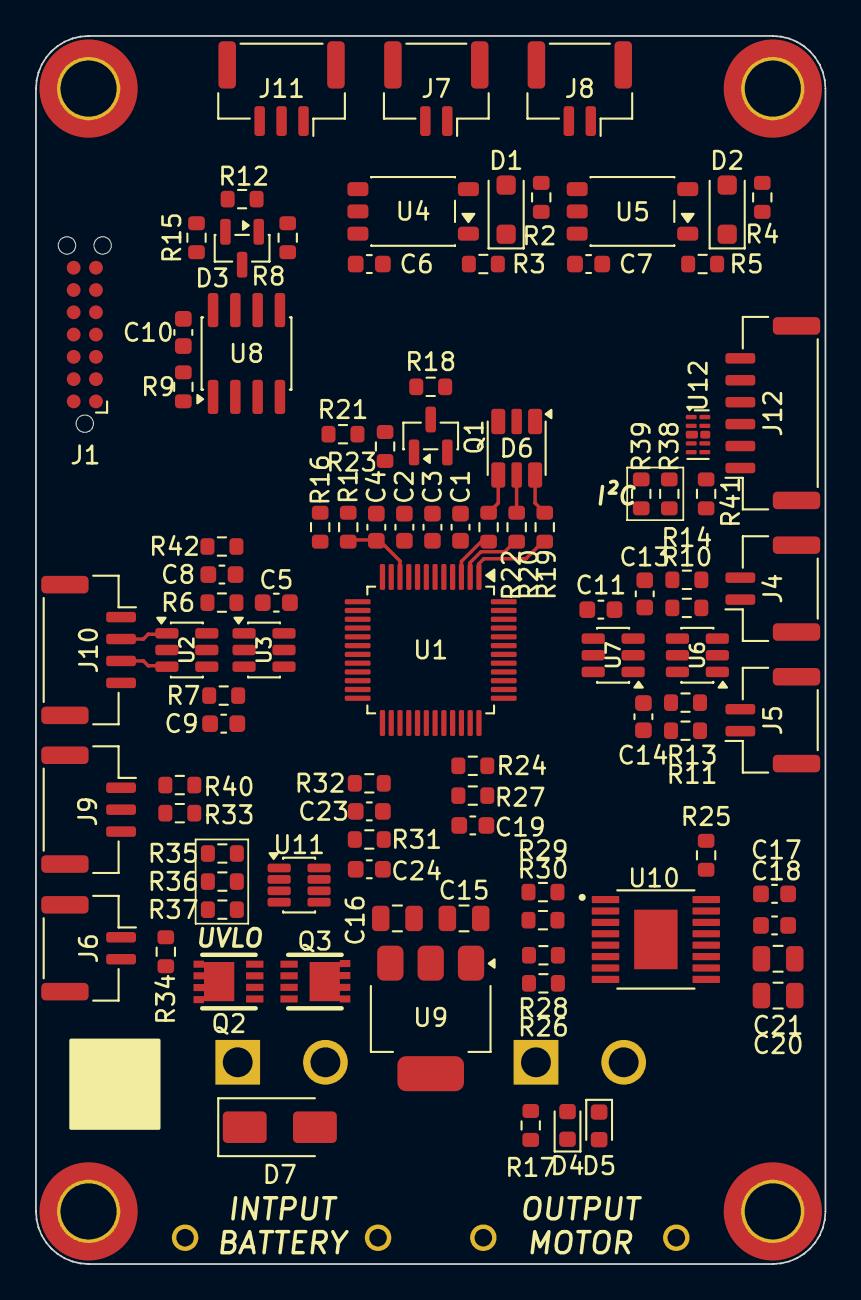
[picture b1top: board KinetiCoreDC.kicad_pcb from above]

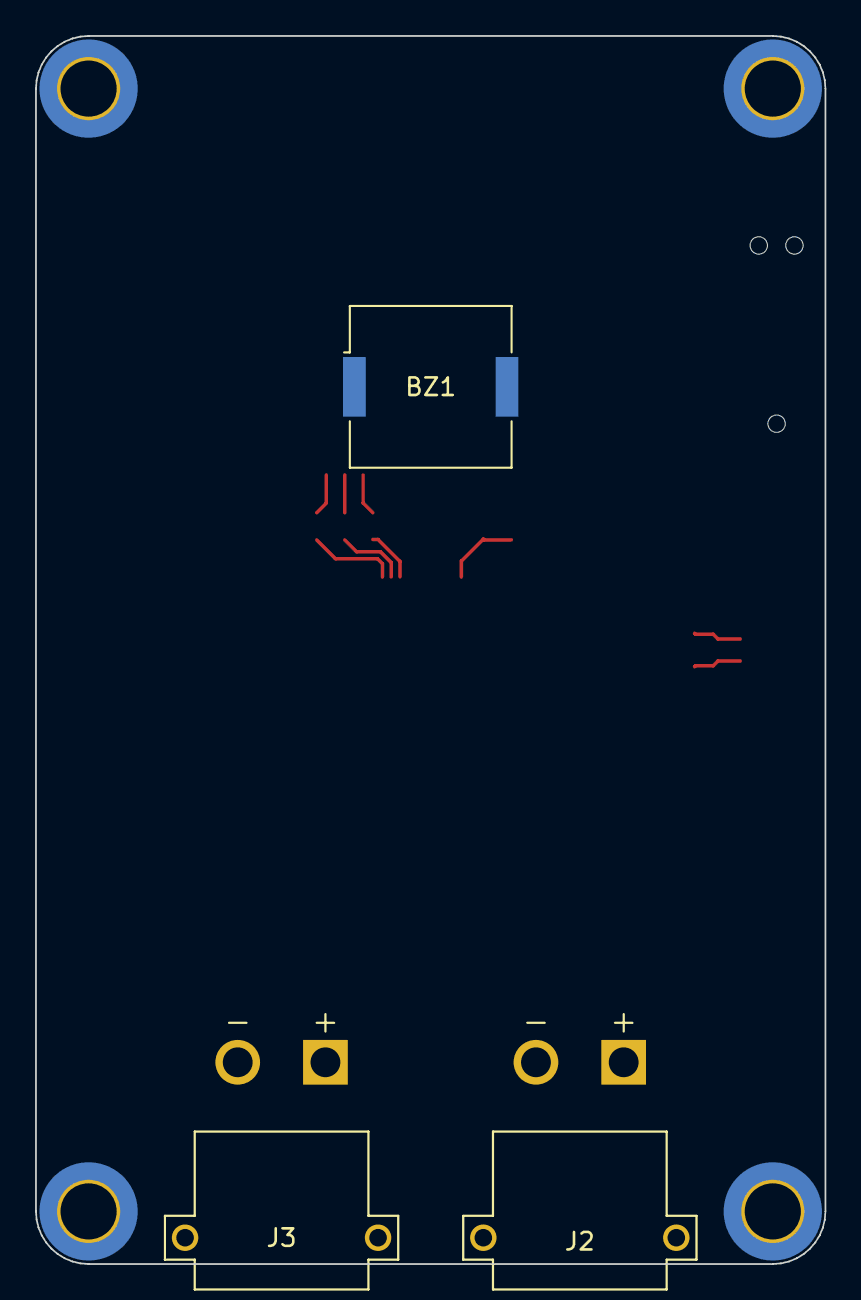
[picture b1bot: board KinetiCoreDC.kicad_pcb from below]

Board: 4 copper layers, 45.0 x 70.0 mm, 103 parts (3 on the bottom side), 86 nets.

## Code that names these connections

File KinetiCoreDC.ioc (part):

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Mcu.Name=STM32G070CBTx
Mcu.Package=LQFP48
Mcu.UserName=STM32G070CBTx
PA1.GPIOParameters=GPIO_Label
PA1.GPIO_Label=RS485_DE
PA1.Mode=Hardware Flow Control (RS485)
PA1.Signal=USART2_DE
PA10.GPIOParameters=GPIO_Label
PA10.GPIO_Label=NFAULT_DRV
PA10.Signal=GPXTI10
PA13.Mode=Serial_Wire
PA13.Signal=SYS_SWDIO
PA14-BOOT0.Mode=Serial_Wire
PA14-BOOT0.Signal=SYS_SWCLK
PA2.GPIOParameters=GPIO_Label
PA2.GPIO_Label=RS485_TX
PA2.Mode=Asynchronous
PA2.Signal=USART2_TX
PA3.GPIOParameters=GPIO_Label
PA3.GPIO_Label=RS485_RX
PA3.Mode=Asynchronous
PA3.Signal=USART2_RX
PA4.GPIOParameters=GPIO_Label
PA4.GPIO_Label=BUZZER
PA4.Signal=S_TIM14_CH1
PA5.GPIOParameters=GPIO_Label
PA5.GPIO_Label=VCP_TX
PA5.Mode=Asynchronous
PA5.Signal=USART3_TX
PA6.GPIOParameters=GPIO_Label
PA6.GPIO_Label=ENC_A
PA6.Signal=S_TIM3_CH1
PA7.GPIOParameters=GPIO_Label
PA7.GPIO_Label=ENC_B
PA7.Signal=S_TIM3_CH2
PA8.GPIOParameters=GPIO_Label
PA8.GPIO_Label=PH/IN2
PA8.Signal=S_TIM1_CH1
PA9.GPIOParameters=GPIO_Label
PA9.GPIO_Label=EN/IN1
PA9.Signal=S_TIM1_CH2
PB0.GPIOParameters=GPIO_Label
PB0.GPIO_Label=VCP_RX
PB0.Mode=Asynchronous
PB0.Signal=USART3_RX
PB10.Mode=IN11
PB10.Signal=ADC1_IN11
PB14.GPIOParameters=GPIO_Label
PB14.GPIO_Label=OPTO1
PB14.Signal=S_TIM15_CH1
PB15.GPIOParameters=GPIO_Label
PB15.GPIO_Label=OPTO2
PB15.Signal=S_TIM15_CH2
PB2.Mode=IN10
PB2.Signal=ADC1_IN10
PB6.Mode=Full_Duplex_Master
PB6.Signal=SPI2_MISO
PB7.Mode=Full_Duplex_Master
PB7.Signal=SPI2_MOSI
PB8.Mode=Full_Duplex_Master
PB8.Signal=SPI2_SCK
PB9.Mode=NSS_Signal_Hard_Output
PB9.Signal=SPI2_NSS
PC13.GPIOParameters=GPIO_Label
PC13.GPIO_Label=BLUE_RGB
PC13.Signal=GPIO_Output
PC14-OSC32_IN\ (PC14).GPIOParameters=GPIO_Label
PC14-OSC32_IN\ (PC14).GPIO_Label=RED_RGB
PC14-OSC32_IN\ (PC14).Signal=GPIO_Output
PC15-OSC32_OUT\ (PC15).GPIOParameters=GPIO_Label
PC15-OSC32_OUT\ (PC15).GPIO_Label=GREEN_RGB
PC15-OSC32_OUT\ (PC15).Signal=GPIO_Output
PC6.GPIOParameters=GPIO_Label
PC6.GPIO_Label=NSLEEP
PC6.Signal=GPIO_Output
PC7.GPIOParameters=GPIO_Label
PC7.GPIO_Label=PMODE
PC7.Signal=GPIO_Output
PD2.GPIOParameters=GPIO_Label
PD2.GPIO_Label=TRIG1
PD2.Signal=GPXTI2
PD3.GPIOParameters=GPIO_Label
PD3.GPIO_Label=TRIG2
PD3.Signal=GPXTI3
RCC.HSE_VALUE=8000000
RCC.SYSCLKFreq_VALUE=16000000
board=custom

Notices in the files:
README.md:
License: CERN-OHL-S-2.0
